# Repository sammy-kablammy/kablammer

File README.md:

# the kablammer

A 36-key split ergo keeb to optimize your efficiency in dynamic heuristic analysis, improving synergy and interpolation of functional pseudo-discrete technical shizzle wizzles. Guaranteed to make you a 1000x front/back/middle end full stack vibe coded prompt engineer or your money back.

Features:
- [x] Reversible PCB
- [x] RP2040 zero microcontrollers (cheap + uses USB C)
- [x] Rotary encoder for volume or scrollwheel
- [x] RJ45 connects the two halves
- [x] Can seat two minifigures for moral support during intense debugging sessions

Case is made in FreeCAD. I just use the same model for both halves, but mirrored. The halves are not exactly the same, so you'll get slightly larger slots than necessary. I use a magsafe sticker on the bottom of each half. Then you can use magsafe phone stands for tenting.

Firmware is in [my QMK fork](https://github.com/sammy-kablammy/qmk_firmware.git).

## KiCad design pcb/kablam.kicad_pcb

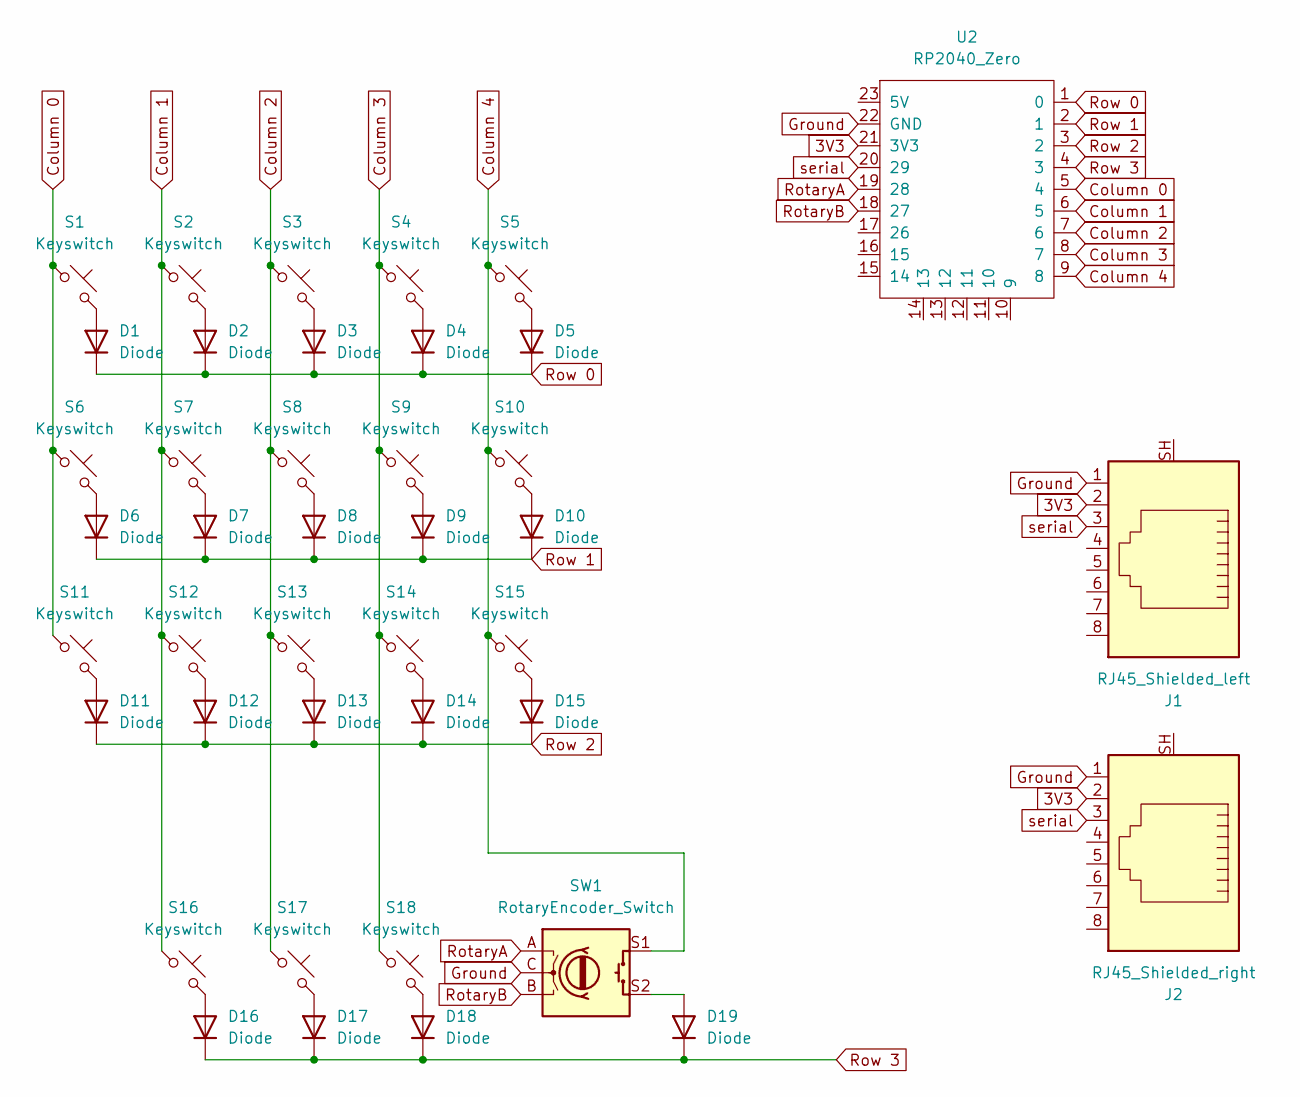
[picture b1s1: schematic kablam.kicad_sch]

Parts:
D1, D2, D3, D4, D5, D6, D7, D8, D9, D10, D11, D12, D13, D14, D15, D16, D17, D18, D19: Diode; Diode_DO-35
J1: RJ45_Shielded_left; RJ45_Ninigi_GE
J2: RJ45_Shielded_right; RJ45_Ninigi_GE
S1, S2, S3, S4, S5, S6, S7, S8, S9, S10, S11, S12, S13, S14, S15, S16, S17, S18: Keyswitch; Hotswap_MX_1.00u_reversible
SW1: RotaryEncoder_Switch; Encoder_EC11_MX
U2: RP2040_Zero

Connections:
3V3: J1.2, J2.2, U2.21 (3V3)
Column 0: S1.1, S6.1, S11.1, U2.5 (4)
Column 1: S2.1, S7.1, S12.1, S16.1, U2.6 (5)
Column 2: S3.1, S8.1, S13.1, S17.1, U2.7 (6)
Column 3: S4.1, S9.1, S14.1, S18.1, U2.8 (7)
Column 4: S5.1, S10.1, S15.1, SW1.S1, U2.9 (8)
Ground: J1.1, J2.1, SW1.C, U2.22 (GND)
unnamed: D1.2 (A), S1.2
unnamed: D2.2 (A), S2.2
unnamed: D3.2 (A), S3.2
unnamed: D4.2 (A), S4.2
unnamed: D5.2 (A), S5.2
unnamed: D6.2 (A), S6.2
unnamed: D7.2 (A), S7.2
unnamed: D8.2 (A), S8.2
unnamed: D9.2 (A), S9.2
unnamed: D10.2 (A), S10.2
unnamed: D11.2 (A), S11.2
unnamed: D12.2 (A), S12.2
unnamed: D13.2 (A), S13.2
unnamed: D14.2 (A), S14.2
unnamed: D15.2 (A), S15.2
unnamed: D16.2 (A), S16.2
unnamed: D17.2 (A), S17.2
unnamed: D18.2 (A), S18.2
unnamed: D19.2 (A), SW1.S2
RotaryA: SW1.A, U2.19 (28)
RotaryB: SW1.B, U2.18 (27)
Row 0: D1.1 (K), D2.1 (K), D3.1 (K), D4.1 (K), D5.1 (K), U2.1 (0)
Row 1: D6.1 (K), D7.1 (K), D8.1 (K), D9.1 (K), D10.1 (K), U2.2 (1)
Row 2: D11.1 (K), D12.1 (K), D13.1 (K), D14.1 (K), D15.1 (K), U2.3 (2)
Row 3: D16.1 (K), D17.1 (K), D18.1 (K), D19.1 (K), U2.4 (3)
serial: J1.3, J2.3, U2.20 (29)

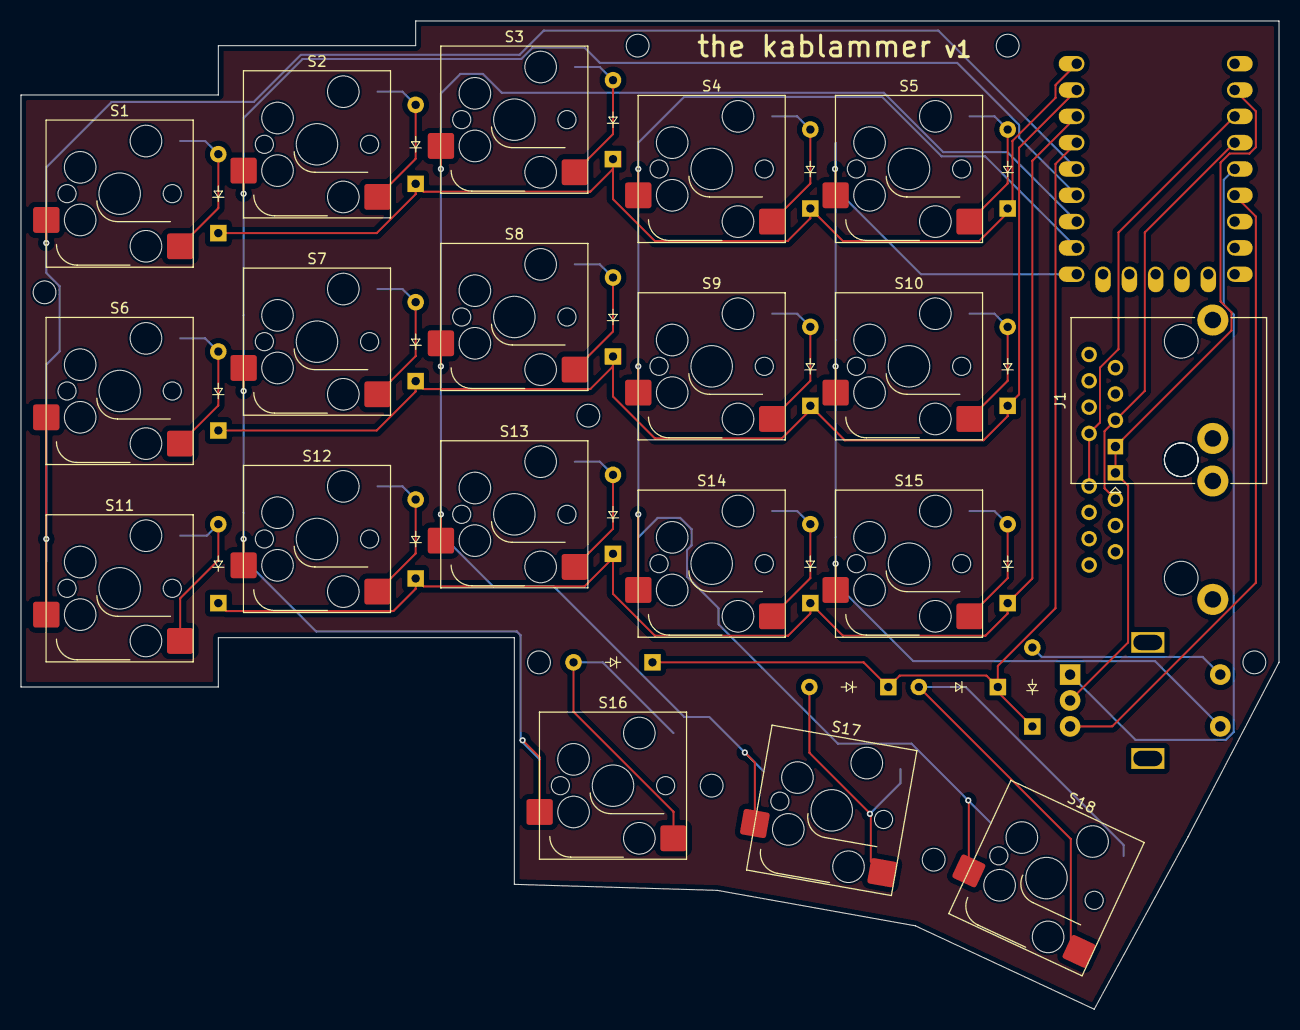
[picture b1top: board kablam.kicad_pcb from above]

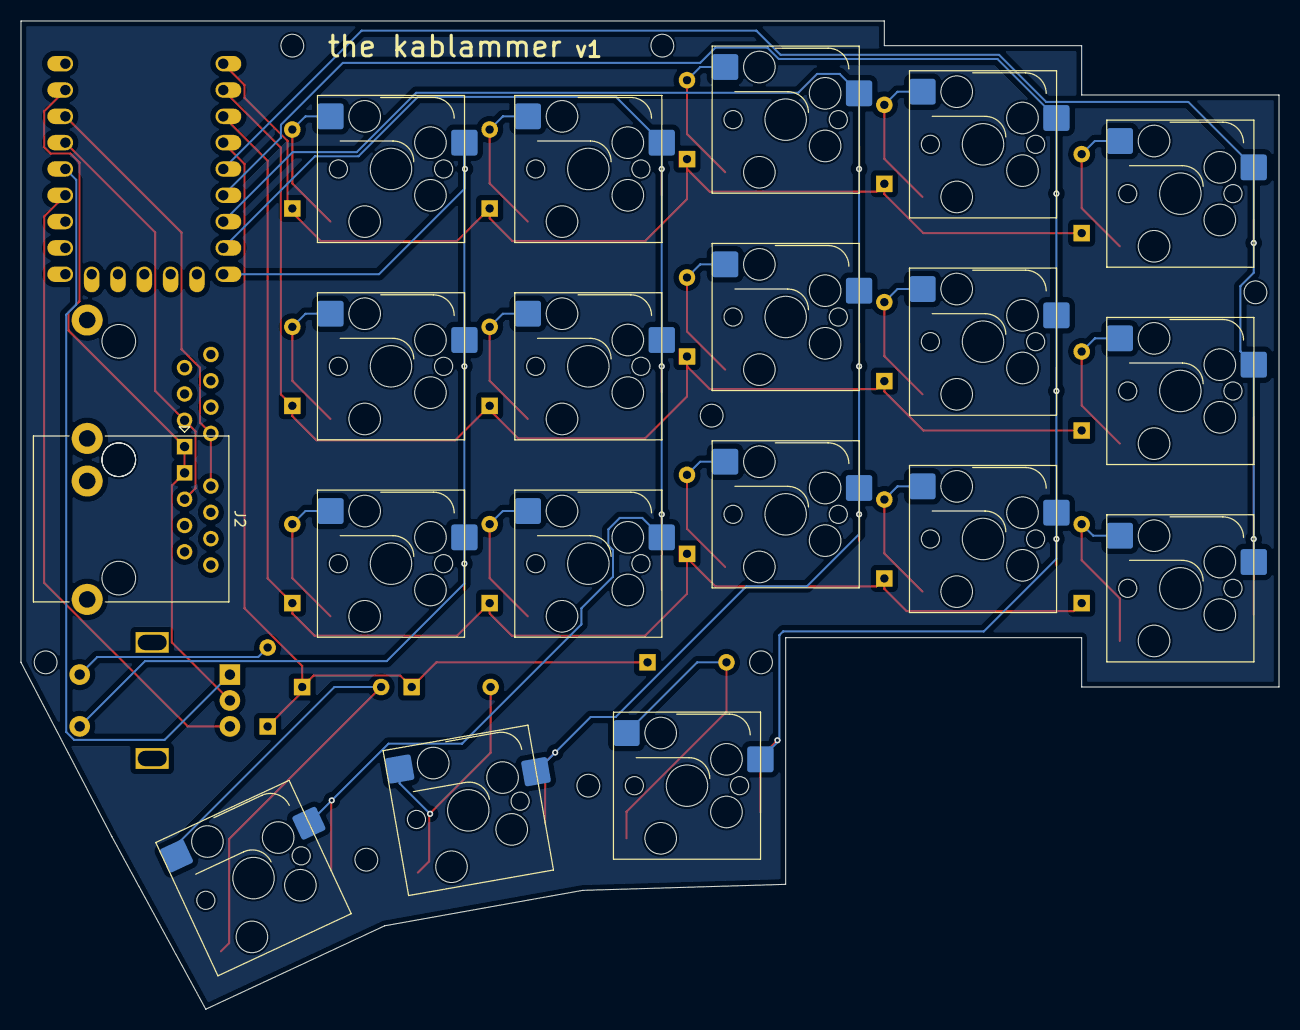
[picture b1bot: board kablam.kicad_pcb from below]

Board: 2 copper layers, 121.4 x 95.4 mm, 41 parts (2 on the bottom side), 33 nets.

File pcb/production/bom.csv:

Designator,Footprint,Quantity,Value,LCSC Part #
"D1, D10, D11, D12, D13, D14, D15, D16, D17, D18, D19, D2, D3, D4, D5, D6, D7, D8, D9",Diode_DO-35,19,Diode,
J1,RJ45_Ninigi_GE,1,RJ45_Shielded_left,
J2,RJ45_Ninigi_GE,1,RJ45_Shielded_right,
"S1, S10, S11, S12, S13, S14, S15, S16, S17, S18, S2, S3, S4, S5, S6, S7, S8, S9",Hotswap_MX_1.00u_reversible,18,Keyswitch,
SW1,Encoder_EC11_MX,1,RotaryEncoder_Switch,
U2,RP2040_Zero,1,RP2040_Zero,
